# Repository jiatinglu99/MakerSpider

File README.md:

MakerSpider
Link to Portfolio: https://docs.google.com/document/d/18AaxFHwQJTH1NfsRH0QoYoiHkLK2H01EVloiZIucRAU/edit?usp=sharing

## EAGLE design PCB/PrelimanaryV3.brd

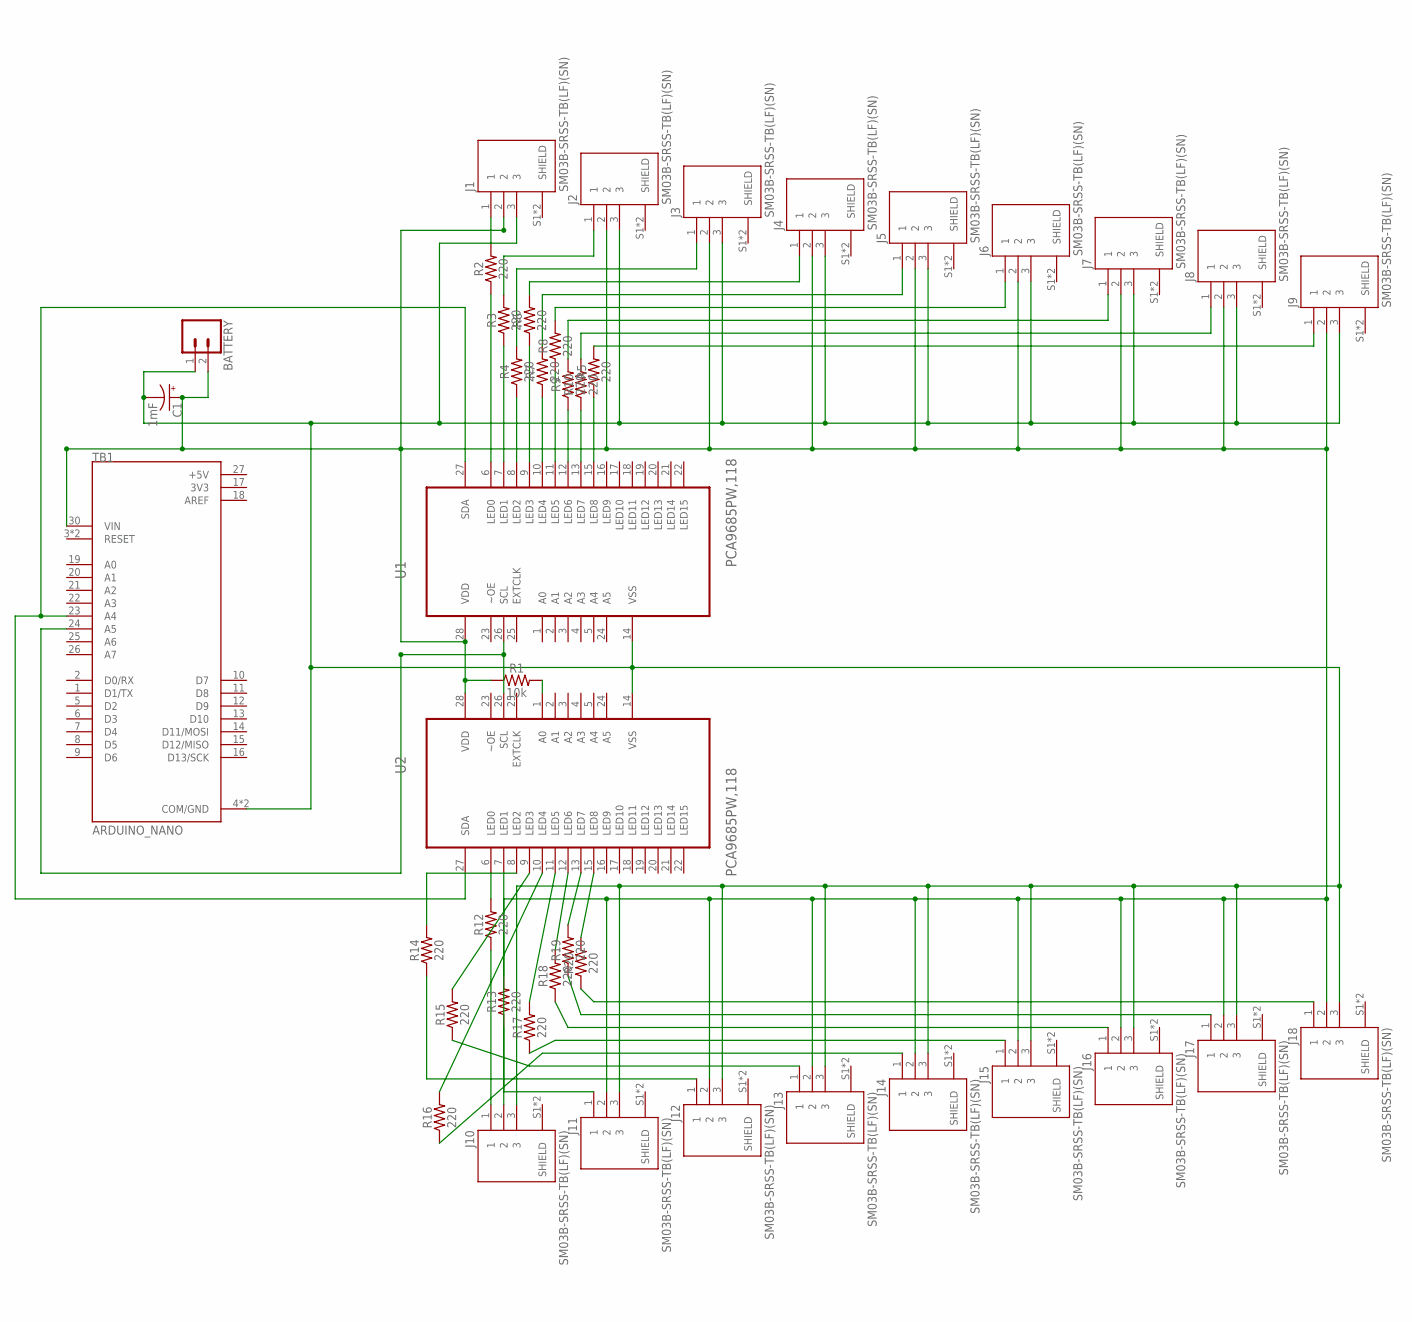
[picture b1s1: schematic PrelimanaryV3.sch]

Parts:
BATTERY: CONN_021X02_NO_SILK; 1X02_NO_SILK
C1: 1mF; CPOL-RADIAL-5MM-10MM
J1, J2, J3, J4, J5, J6, J7, J8, J9, J10, J11, J12, J13, J14, J15, J16, J17, J18: SM03B-SRSS-TB(LF)(SN); JST_SM03B-SRSS-TB(LF)(SN)
R1: 10k; 0402
R2, R3, R4, R5, R6, R7, R8, R9, R10, R12, R13, R14, R15, R16, R17, R18, R19, R20: 220; 0603
TB1: ARDUINO_NANO; SHIELD_ARDUINO_NANO
U1, U2: PCA9685PW,118; SOP65P640X110-28N

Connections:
3V3: TB1.17 (3V3)
+5V: TB1.27 (+5V)
AREF: TB1.18 (AREF)
unnamed: R2.1, U1.6 (LED0)
unnamed: J2.1, R3.2
unnamed: J3.1, R4.2
unnamed: BATTERY.1, C1.-, J1.3, J2.3, J3.3, J4.3, J5.3, J6.3, J7.3, J8.3, J9.3, J10.3, J11.3, J12.3, J13.3, J14.3, J15.3, J16.3, J17.3, J18.3, TB1.4 (COM/GND), TB1.29 (COM/GND), U1.14 (VSS), U2.14 (VSS)
unnamed: TB1.23 (A4), U1.27 (SDA), U2.27 (SDA)
unnamed: TB1.24 (A5), U1.26 (SCL), U2.26 (SCL)
unnamed: J1.1, R2.2
unnamed: J4.1, R6.2
unnamed: J5.1, R7.2
unnamed: J6.1, R8.2
unnamed: J7.1, R9.2
unnamed: J8.1, R10.2
unnamed: J9.1, R5.2
unnamed: J10.1, R12.1
unnamed: J11.1, R13.1
unnamed: J12.1, R14.1
unnamed: J13.1, R15.1
unnamed: J14.1, R16.1
unnamed: J15.1, R17.1
unnamed: J16.1, R18.1
unnamed: J17.1, R19.1
unnamed: J18.1, R20.1
unnamed: BATTERY.2, C1.+, J1.2, J2.2, J3.2, J4.2, J5.2, J6.2, J7.2, J8.2, J9.2, J10.2, J11.2, J12.2, J13.2, J14.2, J15.2, J16.2, J17.2, J18.2, R1.1, TB1.30 (VIN), U1.28 (VDD), U2.28 (VDD)
unnamed: R3.1, U1.7 (LED1)
unnamed: R4.1, U1.8 (LED2)
unnamed: R6.1, U1.9 (LED3)
unnamed: R7.1, U1.10 (LED4)
unnamed: R8.1, U1.11 (LED5)
unnamed: R9.1, U1.12 (LED6)
unnamed: R10.1, U1.13 (LED7)
unnamed: R12.2, U2.6 (LED0)
unnamed: R13.2, U2.7 (LED1)
unnamed: R15.2, U2.9 (LED3)
unnamed: R16.2, U2.10 (LED4)
unnamed: R17.2, U2.11 (LED5)
unnamed: R18.2, U2.12 (LED6)
unnamed: R19.2, U2.13 (LED7)
unnamed: R20.2, U2.15 (LED8)
unnamed: R14.2, U2.8 (LED2)
unnamed: R5.1, U1.15 (LED8)
unnamed: R1.2, U2.1 (A0)

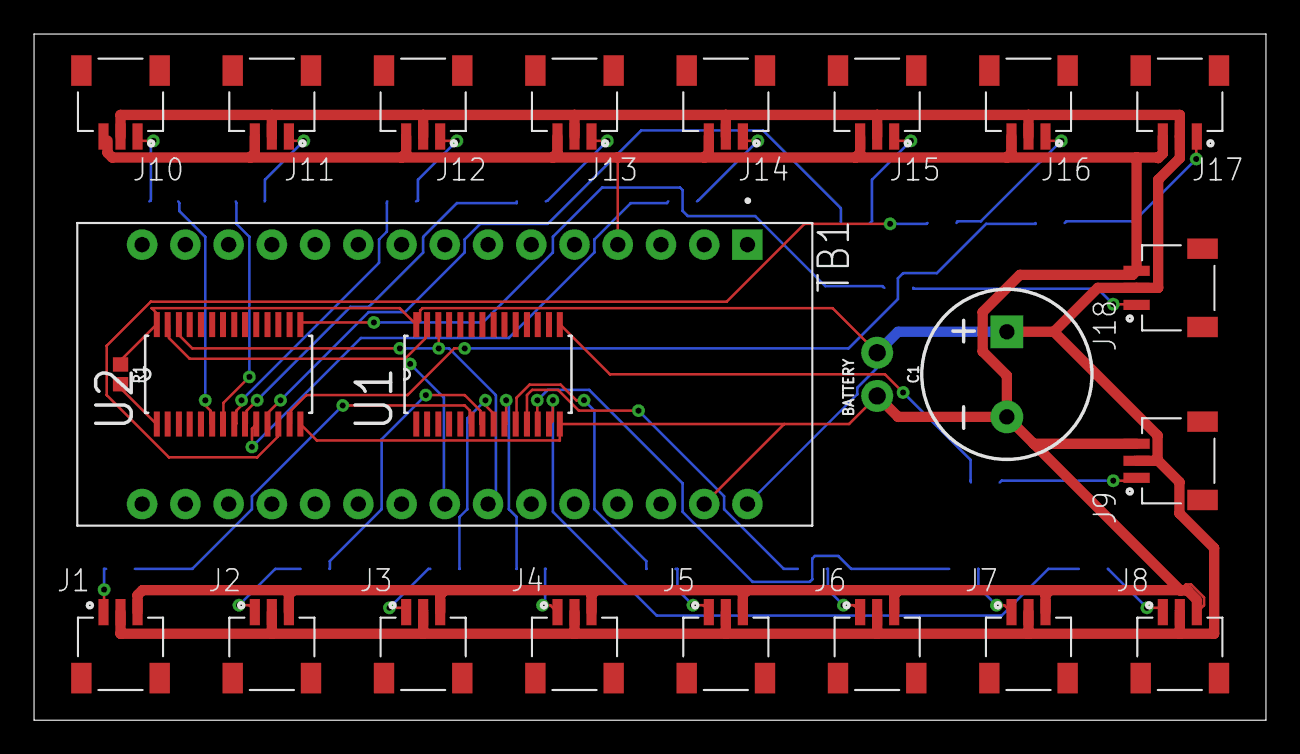
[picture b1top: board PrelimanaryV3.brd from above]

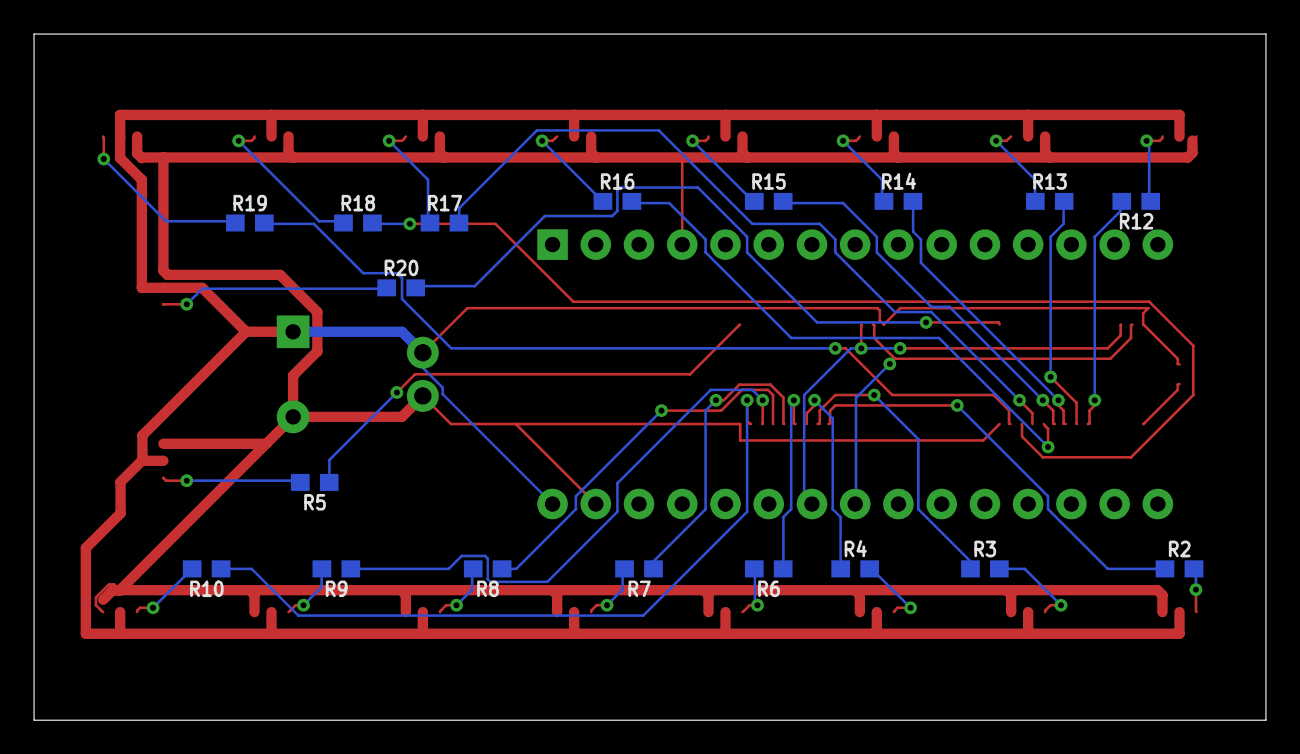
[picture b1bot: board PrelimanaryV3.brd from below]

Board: 2 copper layers, 72.4 x 40.3 mm, 42 parts (18 on the bottom side), 41 nets.

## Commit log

2019-09-25 Add team photos!
2019-12-07 Added PCBs

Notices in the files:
parts and their libraries:
SparkFun-Connectors: Licensing: Creative Commons ShareAlike 4.0 International - https://creativecommons.org/licenses/by-sa/4.0
